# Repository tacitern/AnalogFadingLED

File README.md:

# Hysteresis Oscillator
The primary propuse of this repositor is to explore analog circuit designs which utilize the hysteresis oscillator opamp circuit.

## Current Projects

## TODO/In Progress
- [Analog Fader LED](https://github.com/tacitern/HysteresisOscillator/tree/analogfaderV1pcb/Projects/AnalogFadingLED)
- PWM Simple Motor Speed Control

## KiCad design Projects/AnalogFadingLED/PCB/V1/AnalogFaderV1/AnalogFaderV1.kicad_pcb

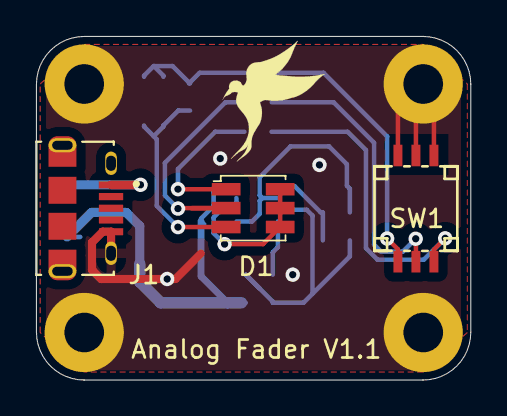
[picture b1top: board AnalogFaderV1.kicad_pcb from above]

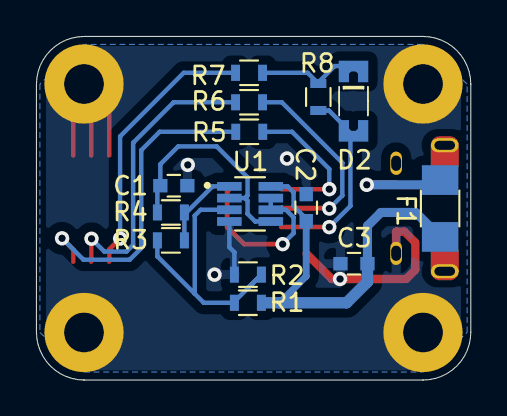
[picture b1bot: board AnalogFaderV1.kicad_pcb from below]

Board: 2 copper layers, 24.1 x 19.1 mm, 17 parts (14 on the bottom side), 14 nets.

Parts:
C1: 10uf; C_0603
C2, C3: 0.1uF; C_0603
D1: CLX6F-FKC; 6-PLCC_3.5x3.5mm
D2: D; SOD-80
F1: Polyfuse_Small; Fuse_SMD1206_Wave
J1: USB_B_Micro; AMPHENOL_10118194-0001LF
R1, R2: 2k; R_0603
R3: 1k; R_0603
R4: 82k; R_0603
R5: 75; R_0603
R6: 105; R_0603
R7: 110 or 63; R_0603
R8: 0; R_0603
SW1: SW_DIP_x03; CVS-03B
U1: LMV358; SOT_23_8_LMV358

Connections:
GND: C1.1, C2.2, C3.2, J1.5, J1.S2, R2.2, SW1.4, SW1.5, SW1.6, U1.4
unnamed: C1.2, R4.2, U1.2, U1.5
unnamed: D1.1, R5.2
unnamed: D1.2, R6.2
unnamed: D1.3, D2.A, R8.2
unnamed: D1.4, D1.5, D1.6, U1.6, U1.7
unnamed: D2.K, R7.2, R8.1
unnamed: F1.1, J1.1
unnamed: R1.2, R2.1, R3.2, U1.3
unnamed: R3.1, R4.1, U1.1
unnamed: R5.1, SW1.3
unnamed: R6.1, SW1.2
unnamed: R7.1, SW1.1
VCC: C2.1, C3.1, F1.2, R1.1, U1.8

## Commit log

2021-01-07 Added initial ideas on project
    Wrote up notes on a hystorisis oscillator which may be used to achieve
    analog LED fading.
    Need to find greatest transistion difference for V1 given Vop=0 and
    Vop=Vcc
2021-01-08 Added python script to check various R1, R2, R3 proportions
    Created a python script to run through the hysteresis transistion points
    for various proportions of R1, R2 and R3. This helped in finding the
    best proportions of R1 to R2 to R3 for the largest hysteresis transition voltages.
    Showed a misinterpertation in the notes previously commited which were corrected in this commit as well.
    An LTSPICE simulation of positive feedback hysteresis resistors was also
    added to verify notes on this sections of the circuit.
2021-01-09 Fixed Math Error
    Corrected really stupid math error in notes
2021-01-10 Finished rough notes for Hysteresis Resistor choice
2021-01-10 Updated LTSPICE Sim
2021-01-13 Added notes on Timming for hysteresis oscillator
2021-01-13 Added PCB files; PCB Schematic
2021-01-18 Added kicad board design files
    Added pcb design files for the analog fader V1
2021-01-19 Completed Kicad PCB for V1
    Finish PCB for V1 of the analog fader circuit.
2021-01-19 Began Doc on hysteresis oscillators
2021-01-21 Added Hysteresis Resistor section to writeup
2021-01-25 Created Projects folder
    Created projects folder moved analog fader LED into the projects folder,
    in preperation of changing the repository name to hysteresis oscillator
    and changing analog fader LED to a project using the hysteresis
    oscillator
2021-01-25 Updated README.md to reflect repository Name change
2021-01-25 Added projects in progress to readme
2021-01-25 Added link to Analog Fader LED Project
2021-01-25 Fixed bad linking
2021-01-27 Added to hysteresis oscillator document
    Added more content to the timing section of the hysteresis oscillator
    document, currently woring on the duty cycle control section of the
    document.
    Added code to V1transistiongraph.py to use the piecewise general voltage
    operation of the RC section of the hysteresis oscillator. Considering
    splitting code into its own python file.
2021-01-27 Added current version of the analog LED fader
    Moving the PCB out of the writeup branch and into its own environment
2021-01-27 Serating the analog fader PCB from the writeup
2021-01-27 Updated PCB to REV 1.1
    Fixed inverted footprint for LMV358
    Added trace length to switch ground connection for easier soldering
2021-01-29 More work on timing section of doc
    Added more to the timing section of the hysteresis oscillator doc
    Added code to generate graphs used in timing section of doc
